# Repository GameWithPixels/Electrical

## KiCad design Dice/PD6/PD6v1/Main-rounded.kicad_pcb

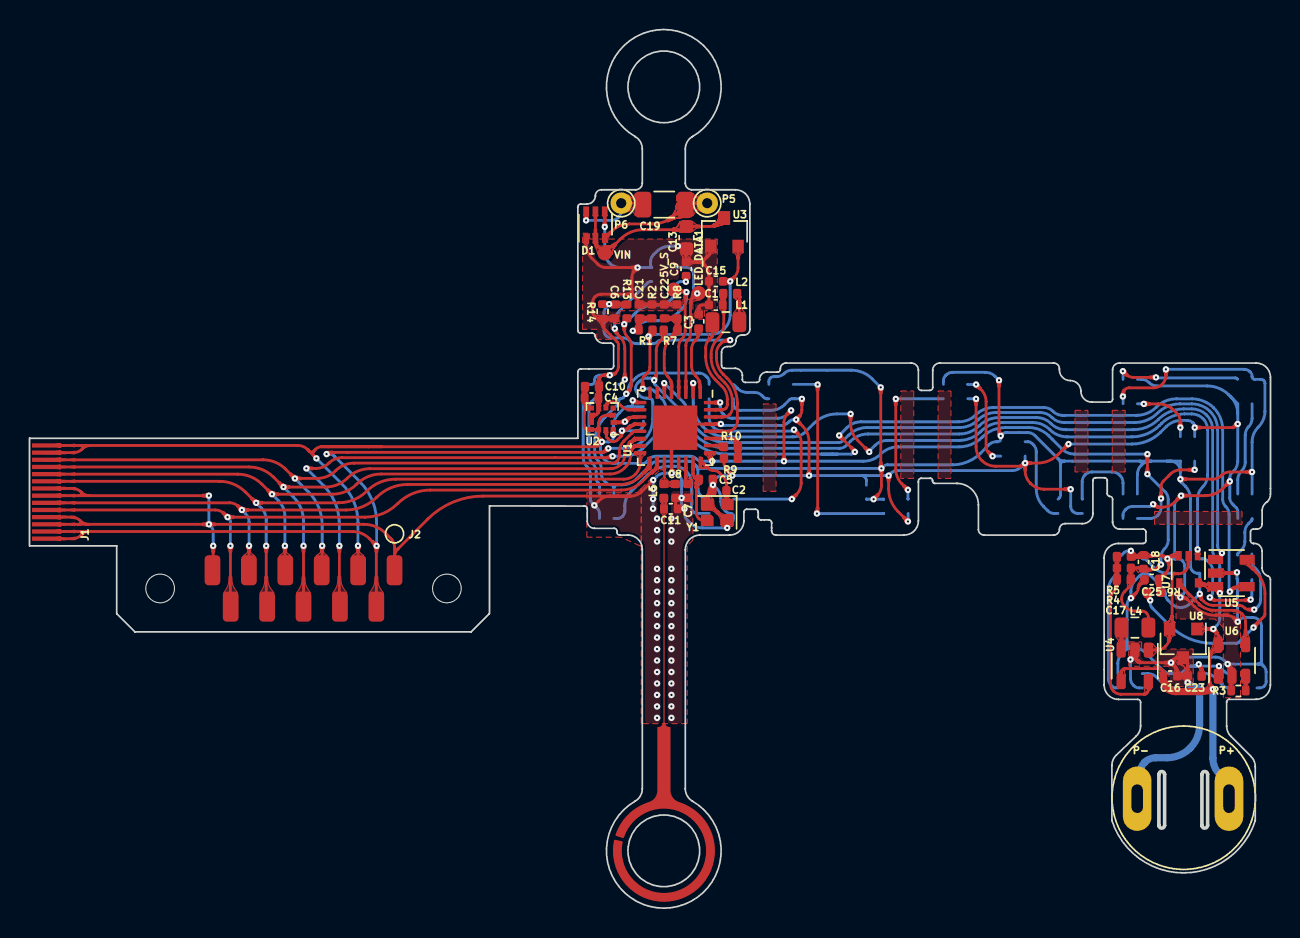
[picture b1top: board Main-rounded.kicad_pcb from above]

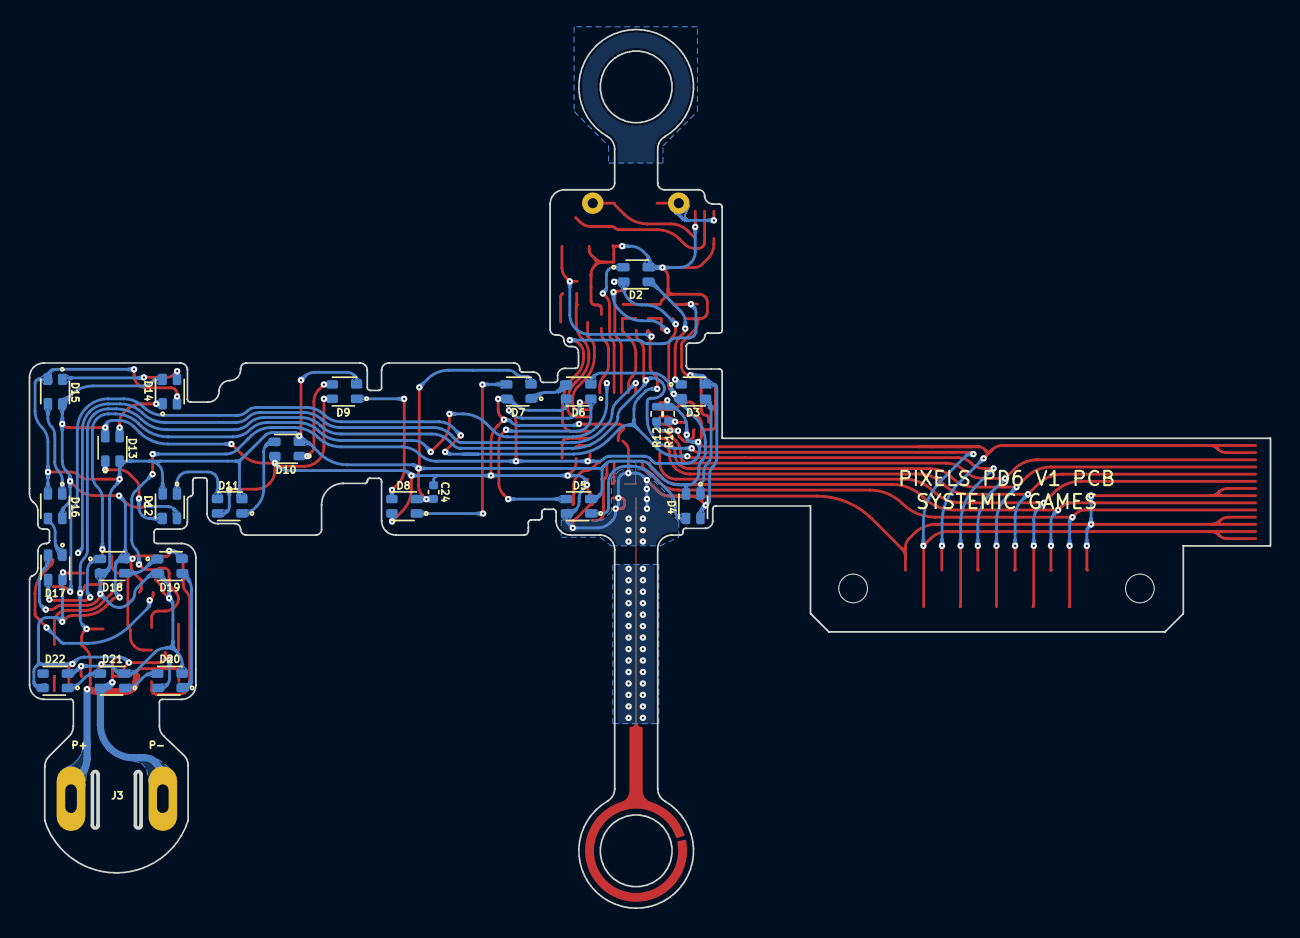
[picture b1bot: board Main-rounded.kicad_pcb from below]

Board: 2 copper layers, 86.6 x 61.3 mm, 80 parts (25 on the bottom side), 60 nets.

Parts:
AE2: ARC; ARC_Antenna
C1, C4, C9, C15, C16, C18: 4.7uF 6.3V 20%; C_0402_1005Metric
C2, C5: 6pF 10V 10%; C_0402_1005Metric
C3, C10, C23, C24, C25: 0.1uF 10V 20%; C_0402_1005Metric
C6, C21, C22: 10nF 25V 10%; C_0402_1005Metric
C7: 100pF NP0 10V 5%; C_0402_1005Metric
C8, C11: ?? NP0; C_0402_1005Metric
C13: 4.7uF 25V 20%; C_0603_1608Metric
C17: 22pF 10V 5%; C_0402_1005Metric
C19: 33nF 50V 5% NP0; C_1206_3216Metric
D1: BAV99S; SOT-363_SC-70-6
D2, D3, D4, D5, D6, D7, D8, D9, D10, D11, D12, D13, D14, D15, D16, D17, D18, D19, D20, D21, D22: TX1812Z_2020
J1: Conn_01x14; FPC_14
J2: Conn_01x11; FPC-POGO-11
J3: Conn_01x02; Hongjie 10100 Connector
L1: 10uH 100mA 10%; L_0805_2012Metric
L2: 15nH 100mA 5%; L_0402_1005Metric
L4: 2.2uH 20mA 10%; L_0805_2012Metric
L5: ??; L_0402_1005Metric
P5: COILA; TestPoint_THTPad_D1.5mm_Drill0.7mm
P6: COILB; TestPoint_THTPad_D1.5mm_Drill0.7mm
R1, R7, R13: 4.02M 1%; R_0402_1005Metric
R2, R8, R14: 10M 1%; R_0402_1005Metric
R3: 10k 5%; R_0402_1005Metric
R4: 402k 1%; R_0402_1005Metric
R5, R10: 100k 1%; R_0402_1005Metric
R6: 22k 1%; R_0402_1005Metric
R9: 150k 1%; R_0402_1005Metric
R12, R16: 2.7k 5%; R_0402_1005Metric
U1: N52810_QFN32; QFN-32-1EP_5x5mm_P0.5mm_EP3.1x3.1mm
U2: KXTJ3-1057; LGA-12_2x2mm_P0.5mm
U3: PJ75AL50SA; SOT-23
U4: LN3406; SOT-23-5
U5: MCP73832T-2ACI/OT; SOT-23-5
U6: MT9700; SOT-23-5
U7: 74AHC1G08; SOT-353_SC-70-5
U8: TMR1366; SOT-23
W13: 5V_S; TEST_PIN
W16: VIN; TEST_PIN
W22: LED_DATA1; TEST_PIN
Y1: 32MHz 40ppm; Crystal_SMD_2016-4Pin_2.0x1.6mm

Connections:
+5V: C15.1, J2.4, R1.1, U3.2 (VOUT), U5.4 (VDD)
+BATT: C16.1, J1.1, J1.2, J2.2, J3.1, R7.1, U4.4 (VIN), U5.3 (VBAT), U6.5 (VIN), U7.5 (VCC), U8.1 (VCC)
/5V_SENSE: C21.1, R1.2, R2.2, U1.4 (P0.04/AIN2), W13.1
/ACC_INT: U1.10 (P0.12), U2.5 (INT)
/ARC_ANTENNA: AE2.1 (A), C11.1, L5.2
/LED_DATA: D2.1 (DIN), U1.3 (P0.01/XL2), W22.1
/LED_EN: U1.2 (P0.00/XL1), U7.1
/Power Supply/LED_EN_OUT: U6.4 (EN), U7.4
/Power Supply/MAG1_: U4.1 (CE), U7.2, U8.2 (OUT)
/SCL: R12.2, U1.12 (P0.15), U2.12 (SCL)
/SDA: R16.2, U1.11 (P0.14), U2.2 (SDA)
/STATS: U1.6 (P0.06), U5.1 (STAT)
/VBAT_SENSE: C22.1, R7.2, R8.1, U1.5 (P0.05/AIN3)
/VLED_SENSE: C6.1, R13.2, R14.1, U1.28 (P0.30/AIN6)
GND: C1.2, C2.1, C3.2, C4.2, C5.1, C6.2, C7.2, C8.2, C9.2, C10.2, C11.2, C13.2, C15.2, C16.2, C18.2, C21.2, C22.2, C23.2, C24.2, C25.2, D1.1 (A1), D1.4 (A3), D2.4 (GND), D3.4 (GND), D4.4 (GND), D5.4 (GND), D6.4 (GND), D7.4 (GND), D8.4 (GND), D9.4 (GND), D10.4 (GND), D11.4 (GND), D12.4 (GND), D13.4 (GND), D14.4 (GND), D15.4 (GND), D16.4 (GND), D17.4 (GND), D18.4 (GND), D19.4 (GND), D20.4 (GND), D21.4 (GND), D22.4 (GND), J1.3, J1.4, J1.7, J1.8, J2.1, J2.11, J3.2, R2.1, R3.2, R5.1, R6.2, R8.2, R9.1, R14.2, U1.20 (VSS), U1.29 (VSS), U1.33 (VSS), U2.6 (GND), U2.8 (GND), U2.9 (GND), U3.1 (VSS), U4.2 (GND), U5.2 (VSS), U6.2 (GND), U7.3 (GND), U8.3 (GND), Y1.2, Y1.4
unnamed: C1.1, L2.2, U1.30 (DEC4)
unnamed: C2.2, U1.24 (XC2), Y1.1
unnamed: C3.1, U1.1 (DEC1)
unnamed: C5.2, U1.23 (XC1), Y1.3
unnamed: C7.1, U1.22 (DEC3)
unnamed: C8.1, L5.1, U1.19 (ANT)
unnamed: C17.2, R4.1, R5.2, U4.5 (FB)
unnamed: C19.1, D1.3 (K1A2), P5.1
unnamed: C19.2, D1.6 (K3A4), P6.1
unnamed: D2.3 (DOUT), D3.1 (DIN)
unnamed: D3.3 (DOUT), D4.1 (DIN)
unnamed: D4.3 (DOUT), D5.1 (DIN)
unnamed: D5.3 (DOUT), D6.1 (DIN)
unnamed: D6.3 (DOUT), D7.1 (DIN)
unnamed: D7.3 (DOUT), D8.1 (DIN)
unnamed: D8.3 (DOUT), D9.1 (DIN)
unnamed: D9.3 (DOUT), D10.1 (DIN)
unnamed: D10.3 (DOUT), D11.1 (DIN)
unnamed: D11.3 (DOUT), D12.1 (DIN)
unnamed: D12.3 (DOUT), D13.1 (DIN)
unnamed: D13.3 (DOUT), D14.1 (DIN)
unnamed: D14.3 (DOUT), D15.1 (DIN)
unnamed: D15.3 (DOUT), D16.1 (DIN)
unnamed: D16.3 (DOUT), D17.1 (DIN)
unnamed: D17.3 (DOUT), D18.1 (DIN)
unnamed: D18.3 (DOUT), D19.1 (DIN)
unnamed: D19.3 (DOUT), D20.1 (DIN)
unnamed: D20.3 (DOUT), D21.1 (DIN)
unnamed: D21.3 (DOUT), D22.1 (DIN)
unnamed: L1.1, U1.31 (DCC)
unnamed: L1.2, L2.1
unnamed: L4.1, U4.3 (LX)
unnamed: R3.1, U6.3 (SET)
unnamed: R6.1, U5.5 (PROG)
unnamed: R9.2, R10.1, U1.27 (P0.28/AIN4)
unnamed: R10.2, U1.26 (P0.25)
RESET: J1.9, J2.8, U1.16 (P0.16)
RXI: J1.10, J2.7, U1.15 (P0.20/TCLK)
SWDCLK: J1.6, J2.9, U1.17 (SWDCLK)
SWDIO: J1.5, J2.10, U1.18 (SWDIO)
SWO: J1.11, J2.6, U1.14 (P0.18/TDATA0)
TXO: J1.12, J2.5, U1.13 (P0.16/TDATA1)
VDC: C9.1, C23.1, C24.1, C25.1, D2.2 (VCC), D3.2 (VCC), D4.2 (VCC), D5.2 (VCC), D6.2 (VCC), D7.2 (VCC), D8.2 (VCC), D9.2 (VCC), D10.2 (VCC), D11.2 (VCC), D12.2 (VCC), D13.2 (VCC), D14.2 (VCC), D15.2 (VCC), D16.2 (VCC), D17.2 (VCC), D18.2 (VCC), D19.2 (VCC), D20.2 (VCC), D21.2 (VCC), D22.2 (VCC), R13.1, U6.1 (VOUT)
VDD: C4.1, C10.1, C17.1, C18.1, J1.13, J1.14, J2.3, L4.2, R4.2, R12.1, R16.1, U1.9 (VDD), U1.25 (VDD), U1.32 (VDD), U2.1 (ADDR), U2.3 (IO_VDD), U2.7 (VDD), U2.10 (VDD), U2.11 (IO_VDD)
VEE: C13.1, D1.2 (K2), D1.5 (K4), U3.3 (VIN), W16.1

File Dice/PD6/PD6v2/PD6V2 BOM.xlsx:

Item | Qty | Reference(s) | Value | Footprint | Generic OK | Manufacturer | Manufacturer Part Number
1 | 1 | AE1 | Antenna_Chip | Pixels-dice:CHIP_ANT | NO | Microgate | MGMA3216H2450-A02
2 | 4 | C1, C4, C15, C18 | 4.7uF 6.3V 20% | Capacitor_SMD:C_0402_1005Metric | YES | Murata | GRM155R60J475ME87D
3 | 2 | C2, C5 | 8pF 10V 10% | Capacitor_SMD:C_0402_1005Metric | YES | Murata | GRT1555C2A8R0DA02
4 | 5 | C3, C10, C23, C24, C25 | 0.1uF 10V 20% | Capacitor_SMD:C_0402_1005Metric | YES | Murata | GRM155R61H104KE19D
5 | 3 | C6, C21, C22 | 10nF 25V 10% | Capacitor_SMD:C_0402_1005Metric | YES | Murata | GRM155R71H103KA88
6 | 1 | C7 | 100pF NP0 10V 5% | Capacitor_SMD:C_0402_1005Metric | YES | Murata | GCM1555C1H101JA16J
7 | 1 | C8 | 0.8pF 10V 5% NP0 | Pixels-dice:0402_RF | YES | Murata | GJM1555C1HR80BB01
8 | 2 | C9, C16 | 10uF 6.3V 20% | Pixels-dice:C_0402_1005Metric | YES | Murata | GRM155R60J106ME05J
10 | 1 | C12 | 0.5pF 10V 5% C0G | Pixels-dice:0402_RF | YES | Murata | GJM1555C1HR50BB01
11 | 1 | C13 | 4.7uF 25V 20% | Capacitor_SMD:C_0603_1608Metric | YES | Murata | GRM188R61E475KE11D
12 | 1 | C17 | 22pF 10V 5% | Capacitor_SMD:C_0402_1005Metric | YES | Murata | GCM1555C1H220JA16J
13 | 1 | C19 | 33nF 50V 5% NP0 | Capacitor_SMD:C_1206_3216Metric | YES | Murata | GRM3195C1H333JA01J
14 | 1 | D1 | BAV99S | Package_TO_SOT_SMD:SOT-363_SC-70-6 | YES | Nexperia | BAV99S,115
15 | 21 | D2, D3, D4, D5, D6, D7, D8, D9, D10, D11, D12, D13, D14, D15, D16, D17, D18, D1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 | TX1812Z_2020 | Pixels-dice:TX1812Z_2020 | NO | TCWIN | TX1812Z 2020
20 | 1 | L1 | 10uH 100mA 10% | Inductor_SMD:L_0805_2012Metric | YES | Murata | LQM21FN100M80L
21 | 1 | L2 | 15nH 100mA 5% | Inductor_SMD:L_0402_1005Metric | YES | Murata | LQG15HS15NJ02D
22 | 1 | L3 | 1.8nH 5% | Pixels-dice:0402_RF | YES | Murata | LQG15HZ1N8C02D
23 | 1 | L4 | 2.2uH 20mA 10% | Inductor_SMD:L_0805_2012Metric | YES | Murata | LQM21PN2R2MC0
24 | 1 | L5 | 3.9nH 5% | Pixels-dice:0402_RF | YES | Murata | LQG15HS3N9B02D
27 | 3 | R1, R7, R13 | 4.02M 1% | Resistor_SMD:R_0402_1005Metric | YES | UNI-ROYAL(Uniroyal Elec) | 0402WGF4024TCE
28 | 3 | R2, R8, R14 | 10M 1% | Resistor_SMD:R_0402_1005Metric | YES | UNI-ROYAL(Uniroyal Elec) | 0402WGF1005TCE
29 | 1 | R3 | 10k 5% | Resistor_SMD:R_0402_1005Metric | YES | UNI-ROYAL(Uniroyal Elec) | 0402WGJ0103TCE
30 | 1 | R4 | 402k 1% | Resistor_SMD:R_0402_1005Metric | YES | UNI-ROYAL(Uniroyal Elec) | 0402WGF4023TCE
31 | 2 | R5, R10 | 100k 1% | Resistor_SMD:R_0402_1005Metric | YES | UNI-ROYAL(Uniroyal Elec) | 0402WGF1003TCE
32 | 1 | R6 | 22k 1% | Resistor_SMD:R_0402_1005Metric | YES | UNI-ROYAL(Uniroyal Elec) | 0402WGF2202TCE
33 | 1 | R9 | 150k 1% | Resistor_SMD:R_0402_1005Metric | YES | UNI-ROYAL(Uniroyal Elec) | 0402WGF1503TCE
34 | 2 | R12, R16 | 2.7k 5% | Resistor_SMD:R_0402_1005Metric | YES | UNI-ROYAL(Uniroyal Elec) | 0402WGJ0272TCE
35 | 1 | U1 | N52810_QFN32 | Package_DFN_QFN:QFN-32-1EP_5x5mm_P0.5mm_EP3.1x3.1mm | NO | Nordic Semiconductor | NRF52810-QCAA-R
36 | 1 | U2 | KXTJ3-1057 | Package_LGA:LGA-12_2x2mm_P0.5mm | NO | Kionix | KXTJ3-1057
37 | 1 | U3 | PJ75AL50SA | Pixels-dice:SOT-23 | NO | PJSEMI | PJ75AL50SA
38 | 1 | U4 | LN3435 | Pixels-dice:SOT-23-5 | NO | NATLINEAR | LN3435
39 | 1 | U5 | MCP73832T-2ACI/OT | Package_TO_SOT_SMD:SOT-23-5 | NO | Microchip | MCP73832T-2ACI/OT
40 | 1 | U6 | MT9700 | Pixels-dice:SOT-23-5 | NO | XI'AN Aerosemi Tech | MT9700
41 | 1 | U7 | SN74LVC1G08 | Pixels-dice:SOT-353_SC-70-5 | YES | UMW(Youtai Semiconductor Co., Ltd.) | SN74LVC1G08DCKR
42 | 1 | U8 | TMR1366 | Package_TO_SOT_SMD:SOT-23 | NO | Multi Dimension | TMR1366S
62 | 1 | Y1 | 32MHz 40ppm | Pixels-dice:Crystal_SMD_2016-4Pin_2.0x1.6mm | YES | Murata | XRCGB32M000F2P00R0

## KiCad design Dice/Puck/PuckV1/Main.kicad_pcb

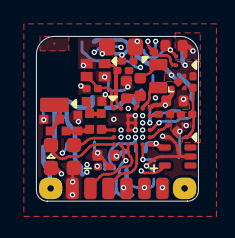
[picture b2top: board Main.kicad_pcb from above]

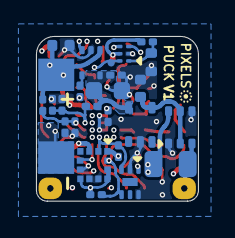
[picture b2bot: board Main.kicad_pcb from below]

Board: 4 copper layers, 9.0 x 9.2 mm, 57 parts (25 on the bottom side), 41 nets.

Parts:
AE1: Antenna_Chip; CHIP_ANT
C1, C4, C18: 4.7uF 10V 20%; C_0402_1005Metric
C2, C5: 8pF 10V 10%; C_0201_0603Metric
C3, C10, C23: 0.1uF 10V 20%; C_0201_0603Metric
C7: 100pF NP0 10V 2%; C_0201_0603Metric
C8: 1.2pF 10V 5% C0G; 0402_RF
C9, C16: 10uF 6.3V 20%; C_0402_1005Metric
C11, C12: DNP; 0402_RF
C13: 4.7uF 25V 20%; C_0402_1005Metric
C15: 22uF 10V 20%; C_0603_1608Metric
C19: 12nF 50V 5% NP0; C_0805_2012Metric
C21, C22: 10nF 25V 10%; C_0201_0603Metric
D1: BAV99S; SOT-363_SC-70-6
J1: Conn_01x02; Batt_409090_Tabs
J2: Conn_01x04; PROG_1.27
J5: Conn_01x06; LED_CONNECTOR_6
L1: 10uH 100mA 20%; C_1.2x1.8
L2: 15nH 100mA 5%; L_0402_1005Metric
L3: 0 Ohm; 0402_RF
L4: 2.2nH 5%; 0402_RF
L5: 3.3nH 5%; 0402_RF
P5: COILA; COIL_CON
P6: COILB; COIL_CON
Q1: ZSPT-Z1608C-06F-Z4; D_0603_1608Metric
R1, R2, R7: 3.9M 1%; R_0201_0603Metric
R4, R5: 10k 1%; R_0201_0603Metric
R6, R10, R11: 5.6k 1%; R_0201_0603Metric
R8: 10M 1%; R_0201_0603Metric
R9: 100k 1%; R_0201_0603Metric
R12: 510R 1%; R_0201_0603Metric
TH1: NTC 100k @ 25C; R_0402_1005Metric
U1: NRF52811-CAAA-R; WLCSP
U2: KXTJ3-1057; LGA-12_2x2mm_P0.5mm
U3: TPS715; SOT-353_SC-70-5
U4: 24C02D6(XBLW); DFN-6-1EP_2x2mm_P0.47
U5: AW35122
U6: ME6230; FPB1_1-4
U7: DS6101; UDFN-4-1EP_1x1mm_P0.65mm_EP0.48x0.48mm
U8: SL1605; SOT-553
U9: XT4051; SOT-553
U10: WAS3157D-6/TR; DFN1109-6
W21: LED2; TEST_PIN
W23: ADC_OUT; TEST_PIN
Y1: 32MHz 40ppm; SX16Y032000B81T001

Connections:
+5V: C15.1, R1.1, R4.1, U3.5 (VOUT), U9.5 (VCC)
+BATT: C16.1, J1.1, R7.1, R12.1, U5.A2 (VIN), U6.3 (CE), U6.4 (VIN), U9.1 (BAT)
/5V_SENSE: C21.1, R1.2, R2.2, U1.D6 (P0.03/AIN1)
/ACC_INT: U1.G5 (P0.12), U2.5 (INT)
/ANTENNA: AE1.1 (FEED), C11.1, L3.2
/ANT_50: C12.1, L3.1, L5.2
/ANT_MID: C8.1, L4.2, L5.1
/ANT_NRF: L4.1, U1.E1 (ANT)
/LED_DATA: J5.2, U1.G3 (P0.16/TDATA1)
/LED_EN: U1.F3 (P0.17), U5.B2 (EN), W21.1
/LED_RETURN: J5.3, U1.G4 (P0.15)
/MAG1_: U1.F5 (P0.11), U8.5 (OUT)
/MAG2_: J5.4, U1.F2 (P0.21)
/NTC_PHOTO_SENSE: U1.E5 (P0.04/AIN2), U10.6 (A), W23.1
/PROG: R6.2, U1.B5 (P0.00/XL1)
/SCL: R10.2, U1.G2 (P0.20/TCLK), U2.12 (SCL), U4.4 (SCL)
/SDA: R11.2, U1.F4 (P0.14), U2.2 (SDA), U4.3 (SDA)
/SENSE_SELECT: U1.E2 (P0.18/TDATA0), U10.4 (S)
/SM: U1.F6 (P0.8), U7.3 (SM)
/STATS: U1.D5 (P0.01/XL2), U9.3 (CHRG)
/VBAT_SENSE: C22.1, R7.2, R8.1, U1.E6 (P0.05/AIN3)
/Wireless Charging/B-: C23.2, J1.2, U7.2 (VSS), U7.5 (PAD)
/Wireless Charging/COILA: C19.1, D1.3 (K1A2), P5.1
/Wireless Charging/COILB: C19.2, D1.6 (K3A4), P6.1
GND: C1.2, C2.1, C3.2, C4.2, C5.1, C7.2, C8.2, C9.2, C10.2, C11.2, C12.2, C13.2, C15.2, C16.2, C18.2, C21.2, C22.2, D1.1 (A1), D1.4 (A3), J2.1, J5.1, Q1.2 (E), R2.1, R4.2, R8.2, TH1.2, U1.B3 (VSS), U1.B4 (VSS), U1.C1 (VSS_PA), U1.D3 (VSS), U1.D4 (VSS), U1.E3 (VSS), U1.E4 (VSS), U2.6 (GND), U2.8 (GND), U2.9 (GND), U3.2 (GND), U4.2 (GND), U4.6 (WP), U5.B1 (GND), U6.2 (VSS), U7.4 (EB-), U8.2 (GND), U9.2 (GND), U10.2 (GND), Y1.2, Y1.4
unnamed: L1.2, L2.1
unnamed: Q1.1 (C), R5.2, U10.3 (B1)
unnamed: L1.1, U1.A5 (DCC)
unnamed: C3.1, U1.B6 (DEC1)
unnamed: C7.1, U1.A3 (DEC2)
unnamed: C1.1, L2.2, U1.A4 (DEC4)
unnamed: C5.2, U1.A1 (XC1), Y1.3
unnamed: C2.2, U1.A2 (XC2), Y1.1
unnamed: C23.1, R12.2, U7.1 (BAT)
unnamed: R6.1, U9.4 (PROG)
unnamed: R9.2, TH1.1, U10.1 (B0)
SWDCLK: J2.4, U1.G1 (SWDCLK)
SWDIO: J2.3, U1.F1 (SWDIO)
VDC: C9.1, J5.6, R5.1, R9.1, U5.A1 (VOUT), U10.5 (VCC)
VDD: C4.1, C10.1, C18.1, J2.2, J5.5, R10.1, R11.1, U1.A6 (VDD), U1.G6 (VDD), U2.1 (ADDR), U2.3 (IO_VDD), U2.7 (VDD), U2.10 (VDD), U2.11 (IO_VDD), U4.1 (VCC), U6.1 (VOUT), U8.4 (VDD)
VEE: C13.1, D1.2 (K2), D1.5 (K4), U3.4 (VIN)
